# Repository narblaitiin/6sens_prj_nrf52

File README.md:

# 6Sens: inSitu Seismic System for Slope Stability Sensing

## Desciption
The goal is to develop a warning system on the analysis of the evolution of the micro-seismic activity generated before the instability is triggered. The method uses a multitude of low-cost seismic sensors deployed in-situ in a network over the possibly unstable zone. The goal is to characterize the temporal evolution of seismic signals detected simultaneously by several sensors (i .e., co-detection). This method uses to its advantage the heterogeneity of the materials and the attenuation of the waves during their propagation in the material.

The design of these sensors is subject to certain technical constraints essential to good
operation of the project:

    - Be autonomous in energy, over a period of several months (so as not to have to return to site, often dangerous).
    - Be robust, reliable and adapted to extreme climatic conditions (cold, hot, humidity).
    - All sensors in the network must be synchronized precisely enough to perform the analysis (about 1/10 second).
    - Be able to communicate information in real time – or near – measurements to a gateway that will retransmit the data to a dedicated website.
    - Be produced at low cost (to install a large-scale network, and have the possibility of to install sensors in hazardous areas with the possibility of losing them).

## Hardware description
### Geophone sensor
The choice fell on omni geometric sensors from Geospace Technologies such Omni-X-LT or GS-ONE. Seismic geophone is a type of sensor that converts ground movement or a kind vibration into voltage, which could be acquired by an acquisition system. The deviation of this mesured voltage from the base line is called the geophone response and is analysed and for monitoring vibration generated by nature in our case.

The frequency response of the geophone is a kind of harmonic oscillator, which is deternined by corner frequency, around 15Hz for the chosen sensors and damping (typically 0.7 for our case).
Our application require the full wave to be sued and the three-component 3C geophones is used (Omni-X-LT or GS-ONE).
For more information, please to refer to : https://www.geospace.com/products/sensors/

### Amplification/Filtering board
The specifications inform us about the bandwidth of the filtering to be carried out: from 20Hz at 100Hz. So we have to build a band-pass filter having an amplification almost constant on this band and rejects frequencies outside this band. Moreover, the signal will have to be amplified in order to obtain a complete dynamic range between 0 and 3.3V without saturation. Below are listed the
parameters of the different filters that will make up the amplification and filtering card :

    - Filter 1 : active bandpass filter, gain : 33dB, low frequency : 7Hz, high frequency : 154Hz
    - Filter 2 : passive low-pass filter, no gain, cut frequency : 106Hz
    - Filter 3 : active low-pass filter, gain : 6dB, cut frequency : 234Hz

### CPU/Radio board for test
The choice fell on Cicerone MKR main board. Move-X Cicerone LoRa/GNSS Board is a high-performance, low-power, Arduino MKR-compatible development board based on the MAMWLE LoRa Module and the u-blox MAX-M10S GNSS Module. The Cicerone Board delivers best-in-class GNSS, long-range wireless connection, and high-performance MCU processing in a low-power solution for optimal battery life. The Cicerone Board allows users to build tracking applications worldwide with meter-level accuracy and to communicate long-range, low-power data via LoRaWAN. The integrated Li-Po charging circuit enables the Cicerone Board to manage battery charging through the USB port.

### CPU/Radio board for POC
The choice was made to manufacture our own PCB. It has three parts: the MAMWLE-01 radio chipset to transmit LoRaWAN packets (based on an STM32WLE5jx), a UWB chipset DW1000 to measure distance between two sensors and an analog part to supply radio chipset (solar panel or/and Li-Po battery). Connectors (Arduino MKR-compatible) have also been added to insert the seismic sensor amplification/filtering board.

## Firmware description
For this project, the use of Zephyr RTOS has been retained. To see what is Zephyr RTOS and how to install it on your computer, go to https://docs.zephyrproject.org/latest/develop/getting_started/index.html (it supports Linux OS, Windows OS and macOS).

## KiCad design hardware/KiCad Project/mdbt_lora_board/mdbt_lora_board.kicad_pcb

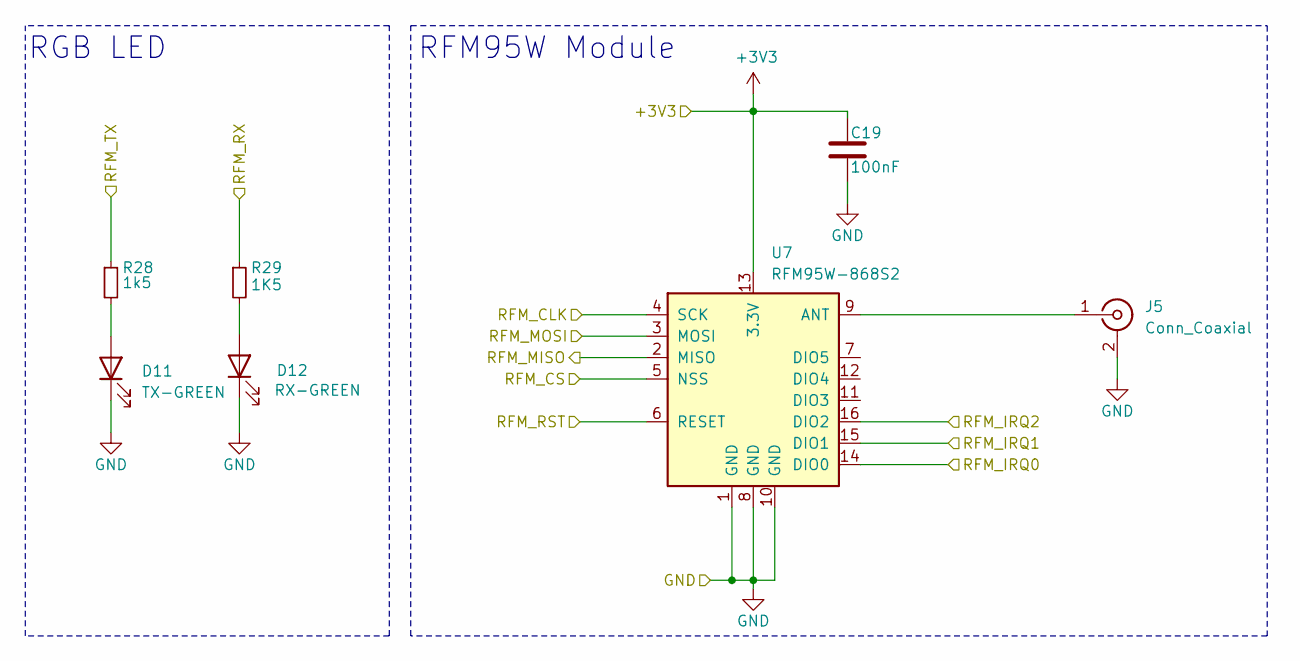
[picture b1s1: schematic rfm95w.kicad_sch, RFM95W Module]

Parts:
C19: 100nF; C_0603_1608Metric; MPN GCM188R71H104JA57D
D11: TX-GREEN; LED_0603_1608Metric; MPN LTST-C191KGKT
D12: RX-GREEN; LED_0603_1608Metric; MPN LTST-C191KGKT
J5: Conn_Coaxial; U.FL_Hirose_U.FL-R-SMT-1_Vertical; MPN U.FL-R-SMT-1(01)
R28: 1k5; R_0603_1608Metric; MPN RC0603FR-071K5L
R29: 1K5; R_0603_1608Metric; MPN RC0603JR-071K5L
U7: RFM95W-868S2; HOPERF_RFM9XW_SMD; MPN RFM95W-868S2

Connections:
+3V3: C19.1, U7.13 (3.3V); also elsewhere on the board
/MDBT50Q-1MV2 (nRF52840)/RFM_CLK: U7.4 (SCK); also elsewhere on the board
/MDBT50Q-1MV2 (nRF52840)/RFM_CS: U7.5 (NSS); also elsewhere on the board
/MDBT50Q-1MV2 (nRF52840)/RFM_IRQ0: U7.14 (DIO0); also elsewhere on the board
/MDBT50Q-1MV2 (nRF52840)/RFM_IRQ1: U7.15 (DIO1); also elsewhere on the board
/MDBT50Q-1MV2 (nRF52840)/RFM_IRQ2: U7.16 (DIO2); also elsewhere on the board
/MDBT50Q-1MV2 (nRF52840)/RFM_MISO: U7.2 (MISO); also elsewhere on the board
/MDBT50Q-1MV2 (nRF52840)/RFM_MOSI: U7.3 (MOSI); also elsewhere on the board
/MDBT50Q-1MV2 (nRF52840)/RFM_RST: U7.6 (RESET); also elsewhere on the board
/MDBT50Q-1MV2 (nRF52840)/RFM_RX: R29.1; also elsewhere on the board
/MDBT50Q-1MV2 (nRF52840)/RFM_TX: R28.1; also elsewhere on the board
GND: C19.2, D11.1 (K), D12.1 (K), J5.2 (Ext), U7.1 (GND), U7.8 (GND), U7.10 (GND); also elsewhere on the board
unnamed: D11.2 (A), R28.2
unnamed: D12.2 (A), R29.2
unnamed: J5.1 (In), U7.9 (ANT)

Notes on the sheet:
RFM95W Module
RGB LED

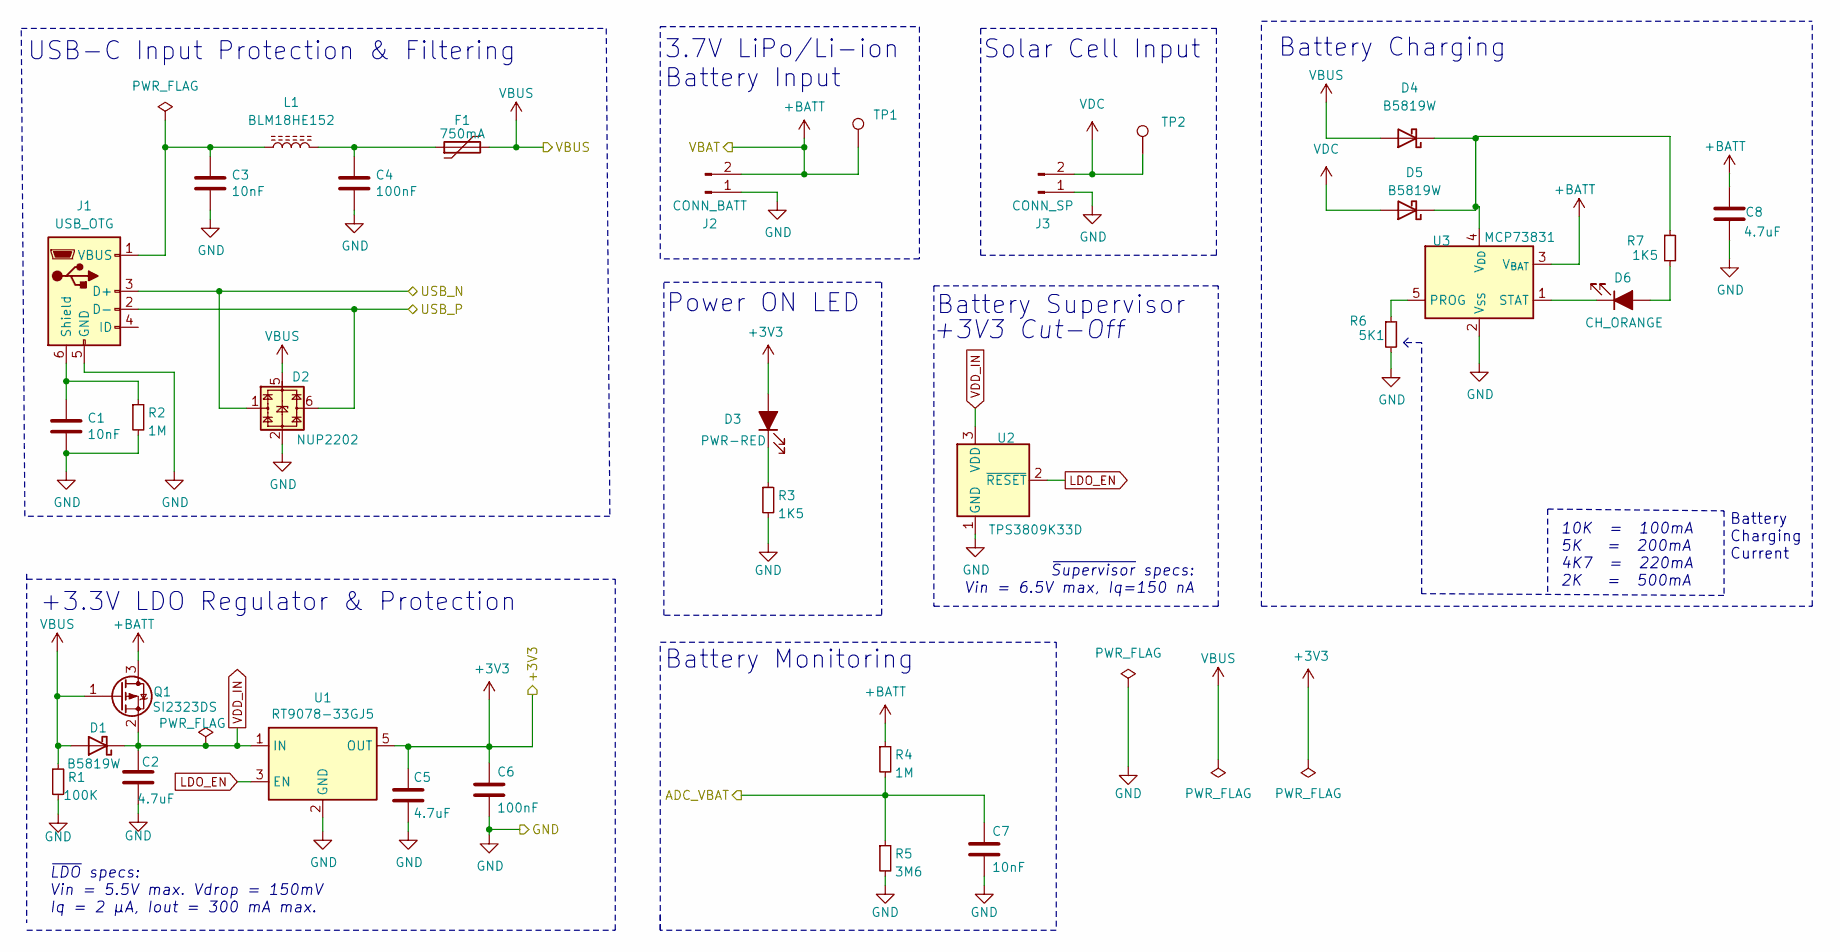
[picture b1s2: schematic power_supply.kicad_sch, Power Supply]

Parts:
C1, C7: 10nF; C_0603_1608Metric; MPN GRM1885C1H103JA01D
C2, C5, C8: 4.7uF; C_0603_1608Metric; MPN GRM188C81E475KE11D
C3: 10nF; C_0603_1608Metric; MPN GRM1885C1H103JA01D; LCSC_Part# Murata Electronics
C4, C6: 100nF; C_0603_1608Metric; MPN GCM188R71H104JA57D
D1, D4, D5: B5819W; D_SOD-123; MPN B5819W
D2: NUP2202; SOT-363_SC-70-6; MPN NUP2202W1T2G
D3: PWR-RED; LED_0603_1608Metric; MPN LTST-C191KRKT
D6: CH_ORANGE; LED_0603_1608Metric; MPN LTST-C191KFKT
F1: 750mA; Fuse_0805_2012Metric; MPN SMD0805B075TF
J1: USB_OTG; USB_Micro-B_Amphenol_10103594-0001LF_Horizontal; MPN 10103594-0001LF
J2: CONN_BATT; PinSocket_1x02_P2.00mm_Vertical; MPN DNM
J3: CONN_SP; PinSocket_1x02_P2.00mm_Vertical; MPN DNM
L1: BLM18HE152; L_0603_1608Metric; MPN BLM18HE152SN1D
Q1: SI2323DS; SOT-23-3; MPN SI2323DS-T1-GE3
R1: 100K; R_0603_1608Metric; MPN RC0603FR-07100KL
R2, R4: 1M; R_0603_1608Metric; MPN RC0603FR-071ML
R3, R7: 1K5; R_0603_1608Metric; MPN RC0603FR-071K5L
R5: 3M6; R_0603_1608Metric; MPN RC0603FR-073M6L
R6: 5K1; R_0603_1608Metric; MPN RC0603FR-075K1L
TP1, TP2: TestPoint; TestPoint_THTPad_D1.5mm_Drill0.7mm
U1: RT9078-33GJ5; TSOT-23-5; MPN RT9078-33GJ5
U2: TPS3809K33D; SOT-23-3; MPN TPS3809K33DBVRG4
U3: MCP73831; SOT-23-5; MPN MCP73831T-2ACI/OT

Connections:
+3V3: C5.1, C6.1, D3.2 (A), U1.5 (OUT); also elsewhere on the board
+BATT: C8.1, J2.2, Q1.3 (D), R4.1, TP1.1, U3.3 (V_{BAT}); also elsewhere on the board
/MDBT50Q-1MV2 (nRF52840)/ADC_VBAT: C7.1, R4.2, R5.1; also elsewhere on the board
/MDBT50Q-1MV2 (nRF52840)/USB_N: D2.1, J1.3 (D+); also elsewhere on the board
/MDBT50Q-1MV2 (nRF52840)/USB_P: D2.6, J1.2 (D-); also elsewhere on the board
GND: C1.1, C2.2, C3.2, C4.2, C5.2, C6.2, C7.2, C8.2, D2.2, J1.5 (GND), J2.1, J3.1, R1.2, R2.2, R3.2, R5.2, R6.2, U1.2 (GND), U2.1 (GND), U3.2 (V_{SS}); also elsewhere on the board
LDO_EN: U1.3 (EN), U2.2 (~RESET)
unnamed: C4.1, F1.1, L1.2
unnamed: D3.1 (K), R3.1
unnamed: D4.1 (K), D5.1 (K), R7.1, U3.4 (V_{DD})
unnamed: D6.2 (A), R7.2
unnamed: D6.1 (K), U3.1 (STAT)
unnamed: C1.2, J1.6 (Shield), R2.1
unnamed: C3.1, J1.1 (VBUS), L1.1
unnamed: R6.1, U3.5 (PROG)
VBUS: D1.2 (A), D2.5, D4.2 (A), F1.2, Q1.1 (G), R1.1; also elsewhere on the board
VDC: D5.2 (A), J3.2, TP2.1
VDD_IN: C2.1, D1.1 (K), Q1.2 (S), U1.1 (IN), U2.3 (VDD)

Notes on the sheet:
Battery Charging
3.7V LiPo/Li-ion Battery Input
Solar Cell Input
Power ON LED
Battery Monitoring
+3.3V LDO Regulator & Protection
10K = 100mA 5K = 200mA 4K7 = 220mA 2K = 500mA
USB-C Input Protection & Filtering
Battery Charging Current
~{Supervisor} specs: Vin = 6.5V max, Iq=150 nA
Battery Supervisor
~{LDO} specs: Vin = 5.5V max. Vdrop = 150mV Iq = 2 μA, Iout = 300 mA max.
+3V3 Cut-Off

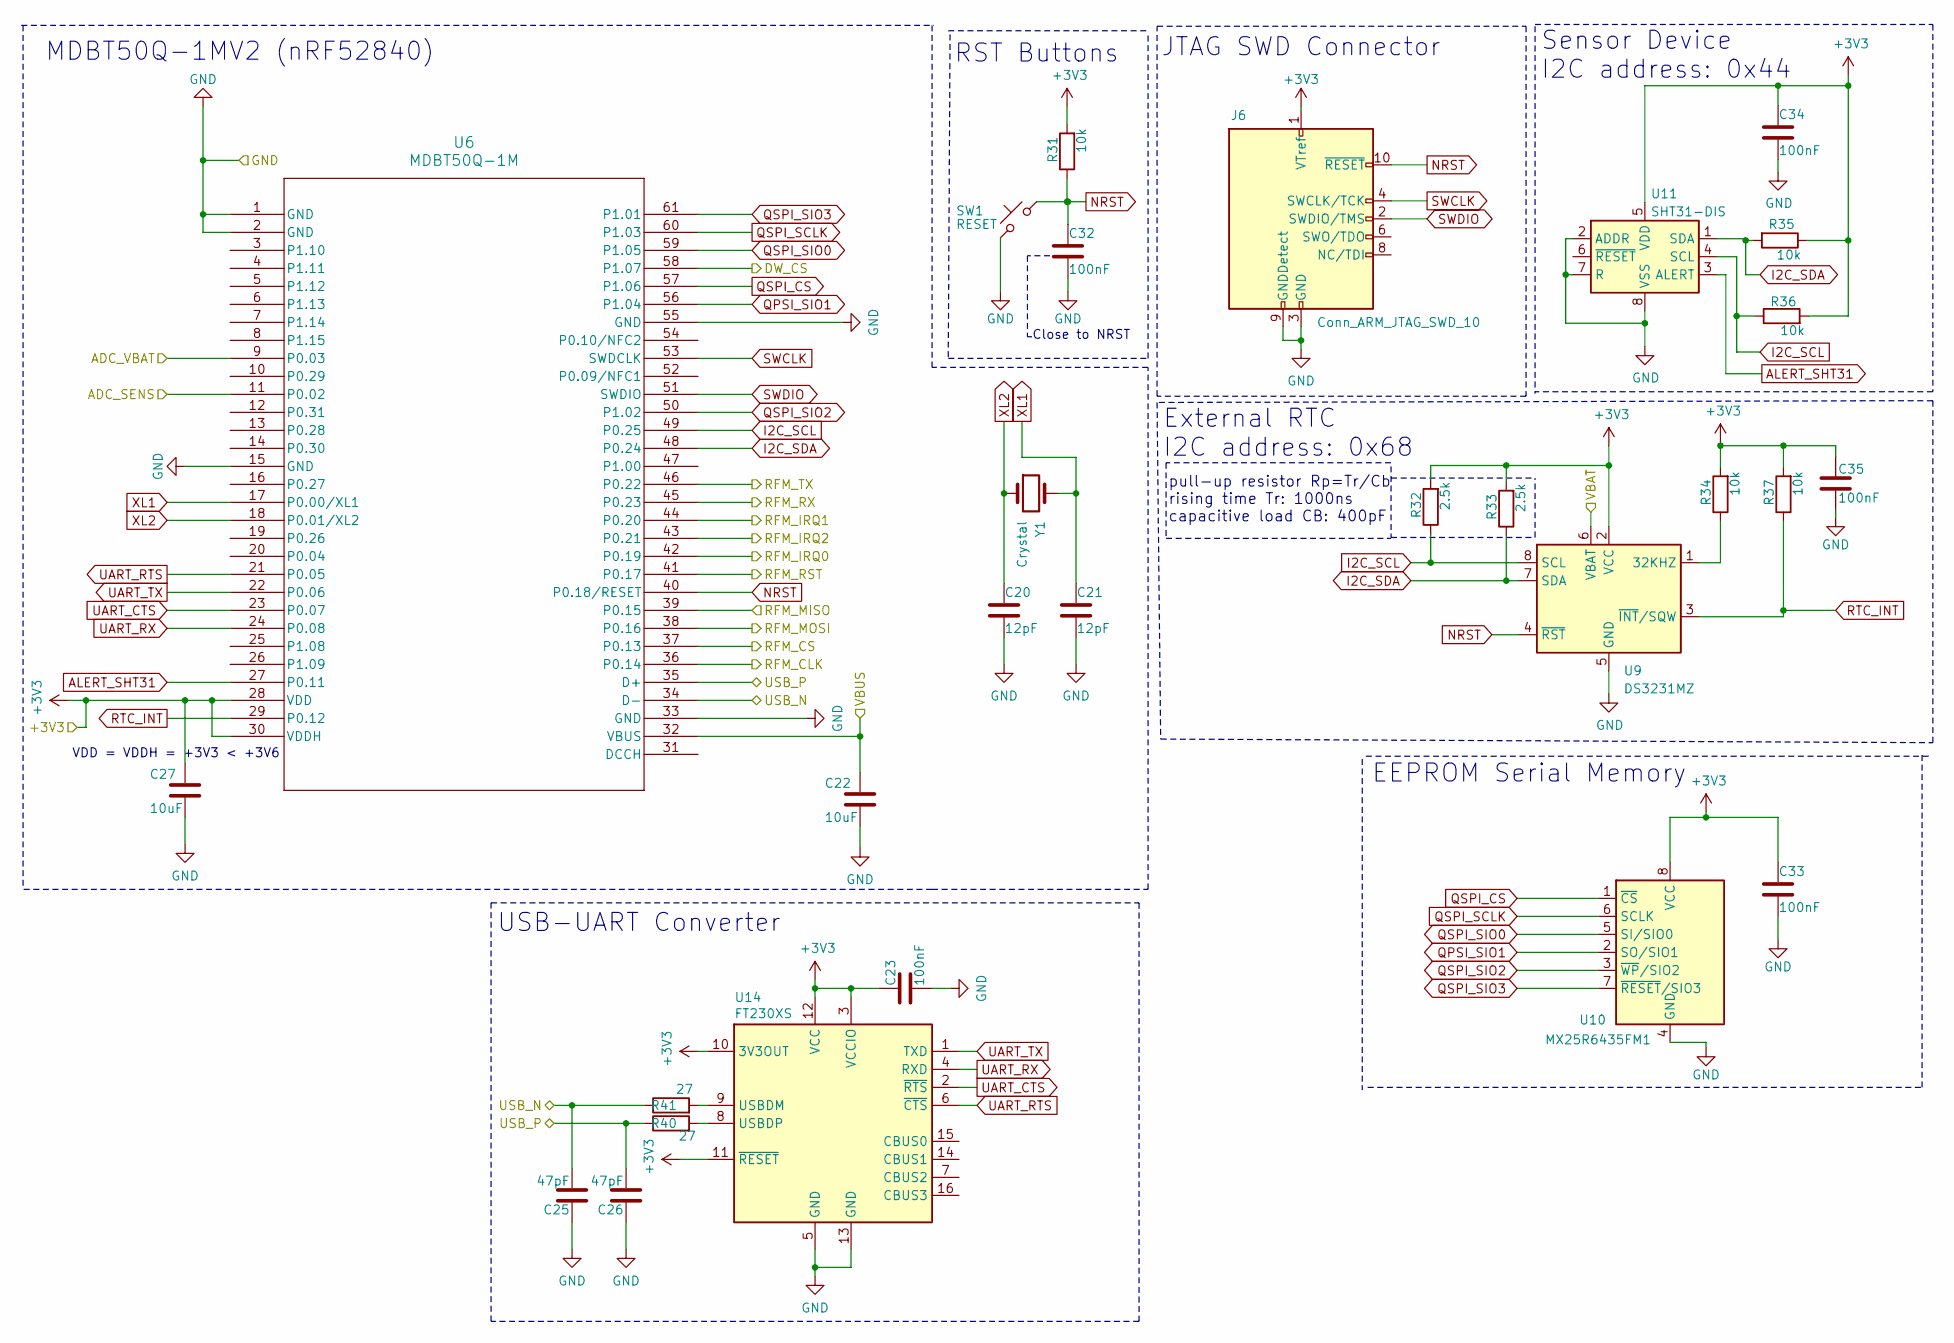
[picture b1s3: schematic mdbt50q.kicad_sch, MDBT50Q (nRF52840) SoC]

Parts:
C20, C21: 12pF; C_0603_1608Metric; MPN GRM1885C1H120JA01D
C22, C27: 10uF; C_0603_1608Metric; MPN GRM188R61E106KA73D
C23, C32, C33, C34, C35: 100nF; C_0603_1608Metric; MPN GCM188R71H104JA57D
C25, C26: 47pF; C_0603_1608Metric; MPN GRM1885C1H470JA01D
J6: Conn_ARM_JTAG_SWD_10; PinHeader_2x05_P1.27mm_Vertical_SMD; MPN 20021121-00010C4LF
R31, R34, R35, R36, R37: 10k; R_0603_1608Metric; MPN RC0603FR-0710KL
R32, R33: 2.5k; R_0603_1608Metric; MPN RC0603FR-072K5L
R40, R41: 27; R_0603_1608Metric; MPN RC0603FR-0727RL
SW1: RESET; SW_Push_1P1T_NO_Vertical_Wuerth_434133025816; MPN 434133025816
U6: MDBT50Q-1M; MDBT50Q-1M_RAY; MPN MDBT50Q-1MV2
U9: DS3231MZ; SOIC-8_3.9x4.9mm_P1.27mm; MPN DS3231MZ+TRL
U10: MX25R6435FM1; SOP-8_5.28x5.23mm_P1.27mm; MPN MX25R6435FM2IL0
U11: SHT31-DIS; Sensirion_DFN-8-1EP_2.5x2.5mm_P0.5mm_EP1.1x1.7mm; MPN SHT31-DIS-P2.5KS
U14: FT230XS; SSOP-16_3.9x4.9mm_P0.635mm; MPN FT230XS-R
Y1: Crystal; Crystal_SMD_3215-2Pin_3.2x1.5mm; MPN CM315D32768HZFT

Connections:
+3V3: C23.1, C27.1, C33.1, C34.1, C35.1, J6.1 (VTref), R31.2, R32.2, R33.2, R34.2, R35.1, R36.2, R37.2, U6.28 (VDD), U6.30 (VDDH), U9.2 (VCC), U10.8 (VCC), U11.5 (VDD), U14.3 (VCCIO), U14.10 (3V3OUT), U14.11 (~RESET), U14.12 (VCC); also elsewhere on the board
+BATT: U9.6 (VBAT); also elsewhere on the board
/Ampliflying and Filtering/ADC_SENS: U6.11 (P0.02); also elsewhere on the board
/MDBT50Q-1MV2 (nRF52840)/ADC_VBAT: U6.9 (P0.03); also elsewhere on the board
/MDBT50Q-1MV2 (nRF52840)/DW_CS: U6.58 (P1.07)
/MDBT50Q-1MV2 (nRF52840)/RFM_CLK: U6.36 (P0.14); also elsewhere on the board
/MDBT50Q-1MV2 (nRF52840)/RFM_CS: U6.37 (P0.13); also elsewhere on the board
/MDBT50Q-1MV2 (nRF52840)/RFM_IRQ0: U6.42 (P0.19); also elsewhere on the board
/MDBT50Q-1MV2 (nRF52840)/RFM_IRQ1: U6.44 (P0.20); also elsewhere on the board
/MDBT50Q-1MV2 (nRF52840)/RFM_IRQ2: U6.43 (P0.21); also elsewhere on the board
/MDBT50Q-1MV2 (nRF52840)/RFM_MISO: U6.39 (P0.15); also elsewhere on the board
/MDBT50Q-1MV2 (nRF52840)/RFM_MOSI: U6.38 (P0.16); also elsewhere on the board
/MDBT50Q-1MV2 (nRF52840)/RFM_RST: U6.41 (P0.17); also elsewhere on the board
/MDBT50Q-1MV2 (nRF52840)/RFM_RX: U6.45 (P0.23); also elsewhere on the board
/MDBT50Q-1MV2 (nRF52840)/RFM_TX: U6.46 (P0.22); also elsewhere on the board
/MDBT50Q-1MV2 (nRF52840)/USB_N: C25.2, R41.1, U6.34 (D-); also elsewhere on the board
/MDBT50Q-1MV2 (nRF52840)/USB_P: C26.2, R40.1, U6.35 (D+); also elsewhere on the board
ALERT_SHT31: U6.27 (P0.11), U11.3 (ALERT)
GND: C20.2, C21.2, C22.2, C23.2, C25.1, C26.1, C27.2, C32.2, C33.2, C34.2, C35.2, J6.3 (GND), J6.5 (GND), J6.9 (GNDDetect), SW1.1, U6.1 (GND), U6.2 (GND), U6.15 (GND), U6.33 (GND), U6.55 (GND), U9.5 (GND), U10.4 (GND), U11.2 (ADDR), U11.7 (R), U11.8 (VSS), U11.9 (VSS), U14.5 (GND), U14.13 (GND); also elsewhere on the board
I2C_SCL: R32.1, R36.1, U6.49 (P0.25), U9.8 (SCL), U11.4 (SCL)
I2C_SDA: R33.1, R35.2, U6.48 (P0.24), U9.7 (SDA), U11.1 (SDA)
NRST: C32.1, J6.10 (~RESET), R31.1, SW1.2, U6.40 (P0.18/RESET), U9.4 (~RST)
unnamed: R34.1, U9.1 (32KHZ)
unnamed: R41.2, U14.9 (USBDM)
unnamed: R40.2, U14.8 (USBDP)
QPSI_SIO1: U6.56 (P1.04), U10.2 (SO/SIO1)
QSPI_CS: U6.57 (P1.06), U10.1 (~CS)
QSPI_SCLK: U6.60 (P1.03), U10.6 (SCLK)
QSPI_SIO0: U6.59 (P1.05), U10.5 (SI/SIO0)
QSPI_SIO2: U6.50 (P1.02), U10.3 (~WP/SIO2)
QSPI_SIO3: U6.61 (P1.01), U10.7 (~RESET/SIO3)
RTC_INT: R37.1, U6.29 (P0.12), U9.3 (~INT/SQW)
SWCLK: J6.4 (SWCLK/TCK), U6.53 (SWDCLK)
SWDIO: J6.2 (SWDIO/TMS), U6.51 (SWDIO)
UART_CTS: U6.23 (P0.07), U14.2 (~RTS)
UART_RTS: U6.21 (P0.05), U14.6 (~CTS)
UART_RX: U6.24 (P0.08), U14.4 (RXD)
UART_TX: U6.22 (P0.06), U14.1 (TXD)
VBUS: C22.1, U6.32 (VBUS); also elsewhere on the board
XL1: C21.1, U6.17 (P0.00/XL1), Y1.2
XL2: C20.1, U6.18 (P0.01/XL2), Y1.1

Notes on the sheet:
MDBT50Q-1MV2 (nRF52840)
JTAG SWD Connector
External RTC I2C address: 0x68
Close to NRST
pull-up resistor Rp=Tr/Cb rising time Tr: 1000ns capacitive load CB: 400pF
Sensor Device I2C address: 0x44
USB-UART Converter
EEPROM Serial Memory
VDD = VDDH = +3V3 < +3V6
RST Buttons

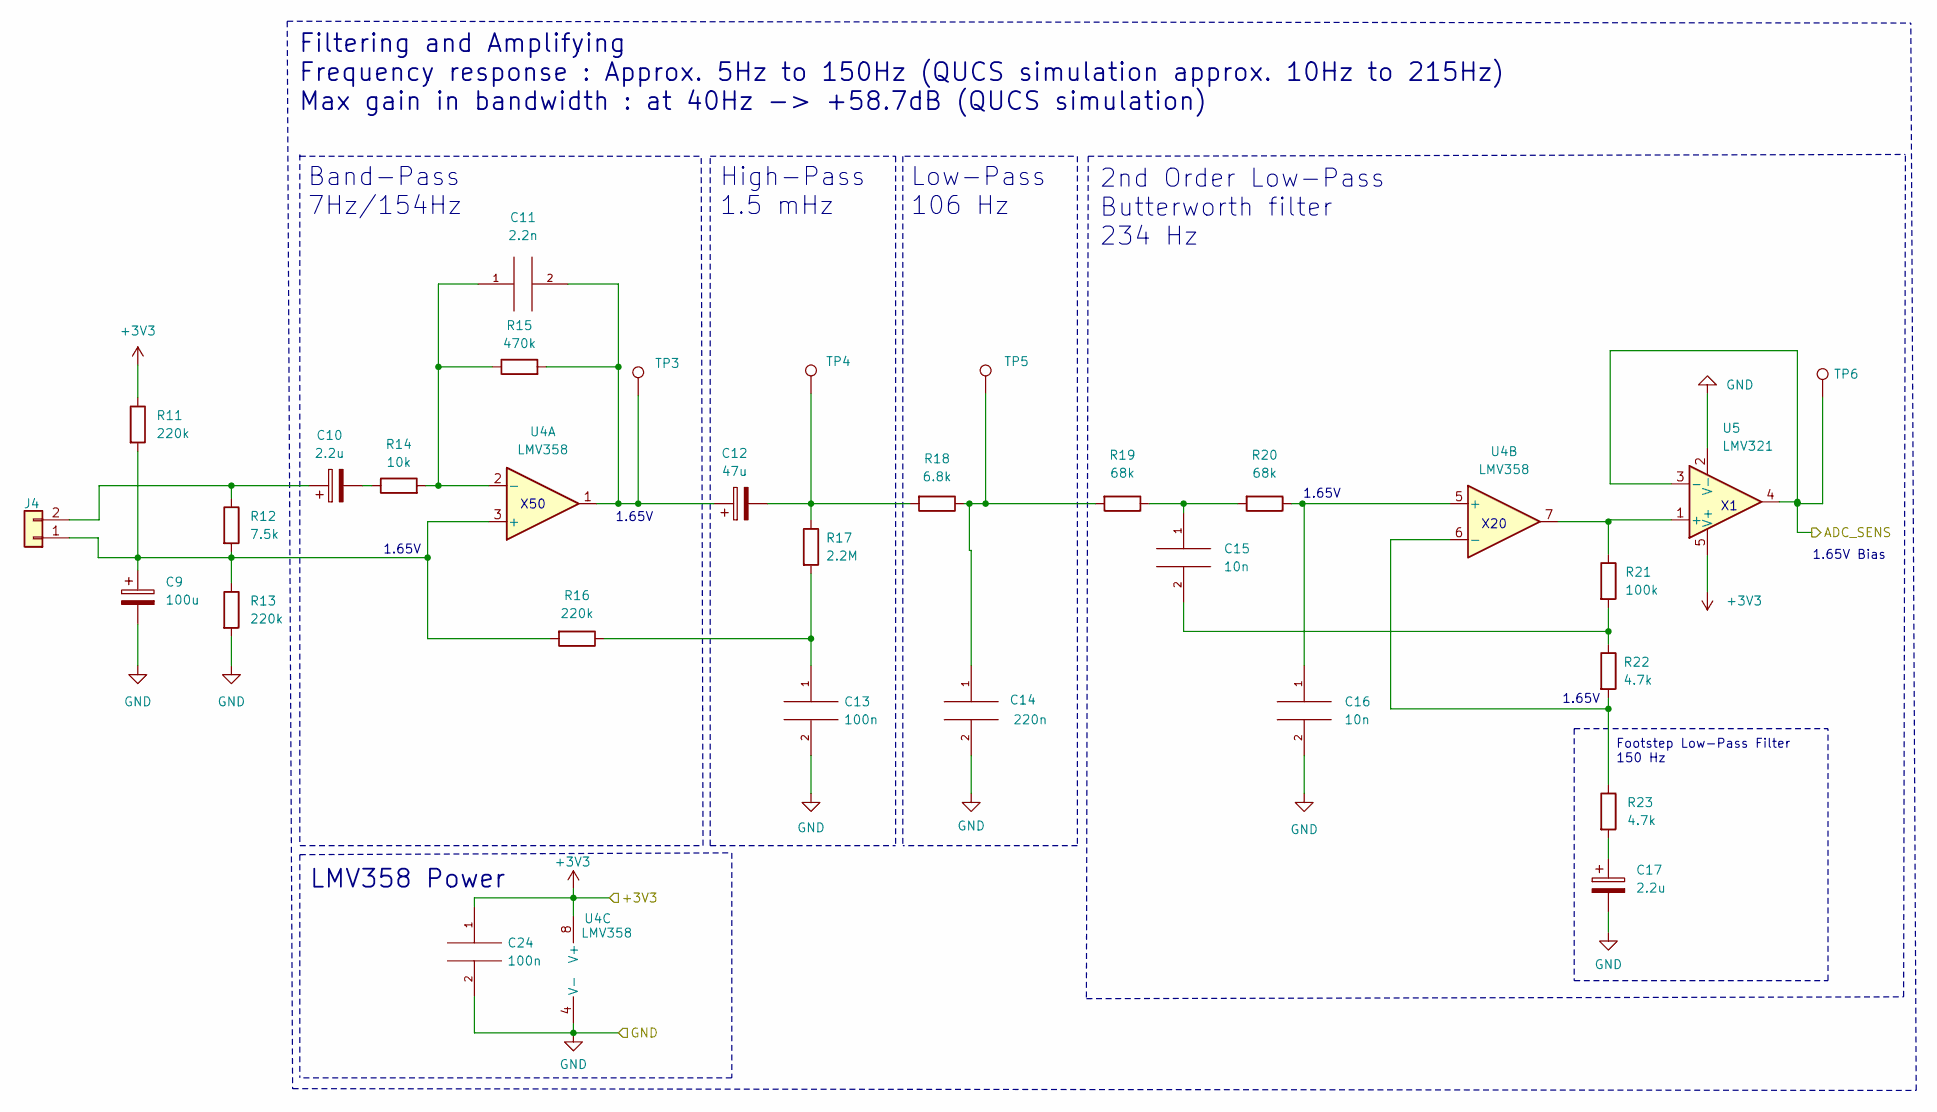
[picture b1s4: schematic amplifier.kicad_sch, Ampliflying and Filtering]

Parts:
C9: 100u; C_1206_3216Metric; MPN GRM31CR60J107KEA8L
C10, C17: 2.2u; C_0603_1608Metric; MPN GRM188R61E225KA12D
C11: 2.2n; C_0603_1608Metric; MPN GRM1885C1H222FA01D
C12: 47u; C_1206_3216Metric; MPN GRM31CR61A476KE15L
C13, C24: 100n; C_0603_1608Metric; MPN GCM188R71H104JA57D
C14: 220n; C_0603_1608Metric; MPN GRM188R71A224JA01D
C15, C16: 10n; C_0603_1608Metric; MPN GRM1885C1H103JA01D
J4: Conn_01x02; JST_PH_S2B-PH-SM4-TB_1x02-1MP_P2.00mm_Horizontal; MPN S2B-PH-SM4-TB
R11, R13, R16: 220k; R_0603_1608Metric; MPN RC0603FR-07220KL
R12: 7.5k; R_0603_1608Metric; MPN RC0603FR-077K5L
R14: 10k; R_0603_1608Metric; MPN RC0603FR-0710KL
R15: 470k; R_0603_1608Metric; MPN RC0603FR-07470KL
R17: 2.2M; R_0603_1608Metric; MPN RC0603FR-072M2L
R18: 6.8k; R_0603_1608Metric; MPN RC0603FR-076K8L
R19, R20: 68k; R_0603_1608Metric; MPN RC0603FR-076K8L
R21: 100k; R_0603_1608Metric; MPN RC0603FR-07100KL
R22, R23: 4.7k; R_0603_1608Metric; MPN RC0603FR-074K7L
TP3, TP4, TP5, TP6: TestPoint; TestPoint_THTPad_D1.5mm_Drill0.7mm
U4: LMV358; SOIC-8_3.9x4.9mm_P1.27mm; MPN LMV358IDRG4
U5: LMV321; SOT-23-5; MPN LMV321IDBVR

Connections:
+3V3: C24.1, R11.1, U4.8 (V+), U5.5 (V+); also elsewhere on the board
/Ampliflying and Filtering/ADC_SENS: TP6.1, U5.3 (-), U5.4; also elsewhere on the board
GND: C9.2, C13.2, C14.2, C16.2, C17.2, C24.2, R13.2, U4.4 (V-), U5.2 (V-); also elsewhere on the board
unnamed: C10.2, R14.1
unnamed: C11.2, C12.1, R15.2, TP3.1, U4.1
unnamed: C12.2, R17.1, R18.2, TP4.1
unnamed: C13.1, R16.1, R17.2
unnamed: C14.1, R18.1, R19.2, TP5.1
unnamed: C15.1, R19.1, R20.2
unnamed: C15.2, R21.2, R22.1
unnamed: C17.1, R23.2
unnamed: C9.1, J4.1, R11.2, R12.2, R13.1, R16.2, U4.3 (+)
unnamed: C10.1, J4.2, R12.1
unnamed: C11.1, R14.2, R15.1, U4.2 (-)
unnamed: C16.1, R20.1, U4.5 (+)
unnamed: R22.2, R23.1, U4.6 (-)
unnamed: R21.1, U4.7, U5.1 (+)

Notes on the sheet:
High-Pass 1.5 mHz
1.65V
LMV358 Power
X20
2nd Order Low-Pass Butterworth filter 234 Hz
1.65V Bias
Low-Pass 106 Hz
Filtering and Amplifying Frequency response : Approx. 5Hz to 150Hz (QUCS simulation approx. 10Hz to 215Hz) Max gain in bandwidth : at 40Hz -> +58.7dB (QUCS simulation)
Footstep Low-Pass Filter 150 Hz
X50
Band-Pass 7Hz/154Hz

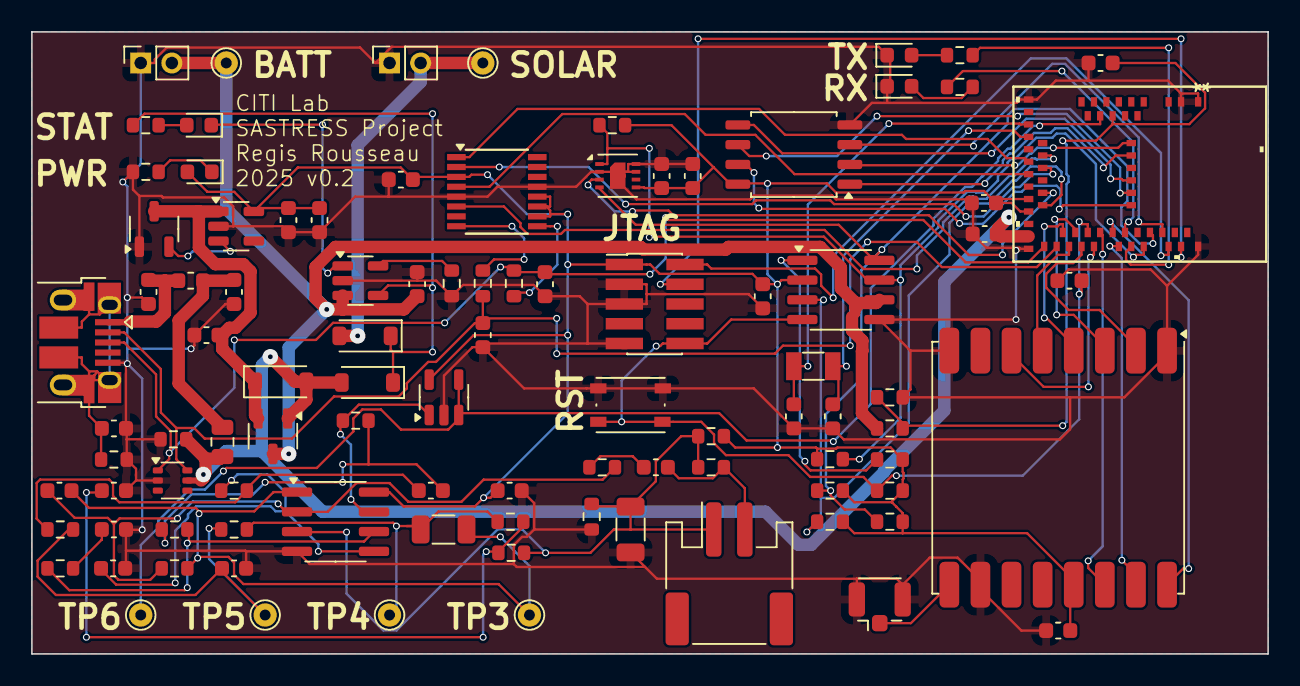
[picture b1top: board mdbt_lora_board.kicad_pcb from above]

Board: 2 copper layers, 79.5 x 40.0 mm, 97 parts (0 on the bottom side), 68 nets.

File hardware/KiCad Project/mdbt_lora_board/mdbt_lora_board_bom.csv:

Reference,Value,Qty,#,MPN,Manufacturer
"C1,C3,C7",10nF,3,1,GRM1885C1H103JA01D,-- mixed values --
"C2,C5,C8",4.7uF,3,2,GRM188C81E475KE11D,Murata Electronics
"C4,C6,C19,C23,C32,C33,C34,C35",100nF,8,3,GCM188R71H104JA57D,Murata Electronics
C9,100u,1,4,GRM31CR60J107KEA8L,Murata Electronics
"C10,C17",2.2u,2,5,GRM188R61E225KA12D,Murata Electronics
C11,2.2n,1,6,GRM1885C1H222FA01D,Murata Electronics
C12,47u,1,7,GRM31CR61A476KE15L,Murata Electronics
"C13,C24",100n,2,8,GCM188R71H104JA57D,Murata Electronics
C14,220n,1,9,GRM188R71A224JA01D,Murata Electronics
"C15,C16",10n,2,10,GRM1885C1H103JA01D,Murata Electronics
"C20,C21",12pF,2,11,GRM1885C1H120JA01D,Murata Electronics
"C22,C27",10uF,2,12,GRM188R61E106KA73D,Murata Electronics
"C25,C26",47pF,2,13,GRM1885C1H470JA01D,Murata Electronics
"D1,D4,D5",B5819W,3,14,B5819W,Good-Ark
D2,NUP2202,1,15,NUP2202W1T2G,Onsemi
D3,PWR-RED,1,16,LTST-C191KRKT,Lite-On Inc
D6,CH_ORANGE,1,17,LTST-C191KFKT,Lite-On Inc
D11,TX-GREEN,1,18,LTST-C191KGKT,Lite-On Inc
D12,RX-GREEN,1,19,LTST-C191KGKT,Lite-On Inc
F1,750mA,1,20,SMD0805B075TF,Yageo
J1,USB_OTG,1,21,10103594-0001LF,Amphenol ICC (FCI)
J2,CONN_BATT,1,22,DNM,
J3,CONN_SP,1,23,DNM,
J4,Conn_01x02,1,24,S2B-PH-SM4-TB,JST Sales America Inc
J5,Conn_Coaxial,1,25,U.FL-R-SMT-1(01),Hirose Electric Co Ltd
J6,Conn_ARM_JTAG_SWD_10,1,26,20021121-00010C4LF,Amphenol ICC (FCI)
L1,BLM18HE152,1,27,BLM18HE152SN1D,Murata Electronics
Q1,SI2323DS,1,28,SI2323DS-T1-GE3,Vishay Siliconix
R1,100K,1,29,RC0603FR-07100KL,Yageo
"R2,R4",1M,2,30,RC0603FR-071ML,Yageo
"R3,R7,R29",1K5,3,31,RC0603FR-072K49L,Yageo
R5,3M6,1,32,RC0603FR-073M6L,Yageo
R6,5K1,1,33,RC0603FR-075K1L,Yageo
"R11,R13,R16",220k,3,34,RC0603FR-07220KL,Yageo
R12,7.5k,1,35,RC0603FR-077K5L,Yageo
"R14,R31,R34,R35,R36,R37",10k,6,36,RC0603FR-0710KL,Yageo
R15,470k,1,37,RC0603FR-07470KL,Yageo
R17,2.2M,1,38,RC0603FR-072M2L,Yageo
R18,6.8k,1,39,RC0603FR-076K8L,Yageo
"R19,R20",68k,2,40,RC0603FR-076K8L,Yageo
R21,100k,1,41,RC0603FR-07100KL,Yageo
"R22,R23",4.7k,2,42,RC0603FR-074K7L,Yageo
R28,1k5,1,43,RC0603FR-071K5L,Yageo
"R32,R33",2.49k,2,44,RC0603FR-072K49L,Yageo
"R40,R41",27,2,45,RC0603FR-0727RL,Yageo
SW1,RESET,1,46,434133025816,Wurth Elektronik
"TP1,TP2,TP3,TP4,TP5,TP6",TestPoint,6,47,,
U1,RT9078-33GJ5,1,48,RT9078-33GJ5,Richtek USA Inc
U2,TPS3809K33D,1,49,TPS3809K33DBVRG4,Texas Instrument
U3,MCP73831,1,50,MCP73831T-2ACI/OT,Microchip Technology
U4,LMV358,1,51,LMV358IDRG4,Texas Instrument
U5,LMV321,1,52,LMV321IDBVR,Texas Instrument
U6,MDBT50Q-1M,1,53,MDBT50Q-1MV2,Raytac
U7,RFM95W-868S2,1,54,RFM95W-868S2,RF Solutions
U9,DS3231MZ,1,55, DS3231MZ+TRL,Analog Device
U10,MX25R6435FM1,1,56,MX25R6435FM2IL0,Macronix
U11,SHT31-DIS,1,57,SHT31-DIS-P2.5KS,Sensirion AG
U14,FT230XS,1,58,FT230XS-R,FTDI
Y1,Crystal,1,59,CM315D32768HZFT,Citizen Finedevice

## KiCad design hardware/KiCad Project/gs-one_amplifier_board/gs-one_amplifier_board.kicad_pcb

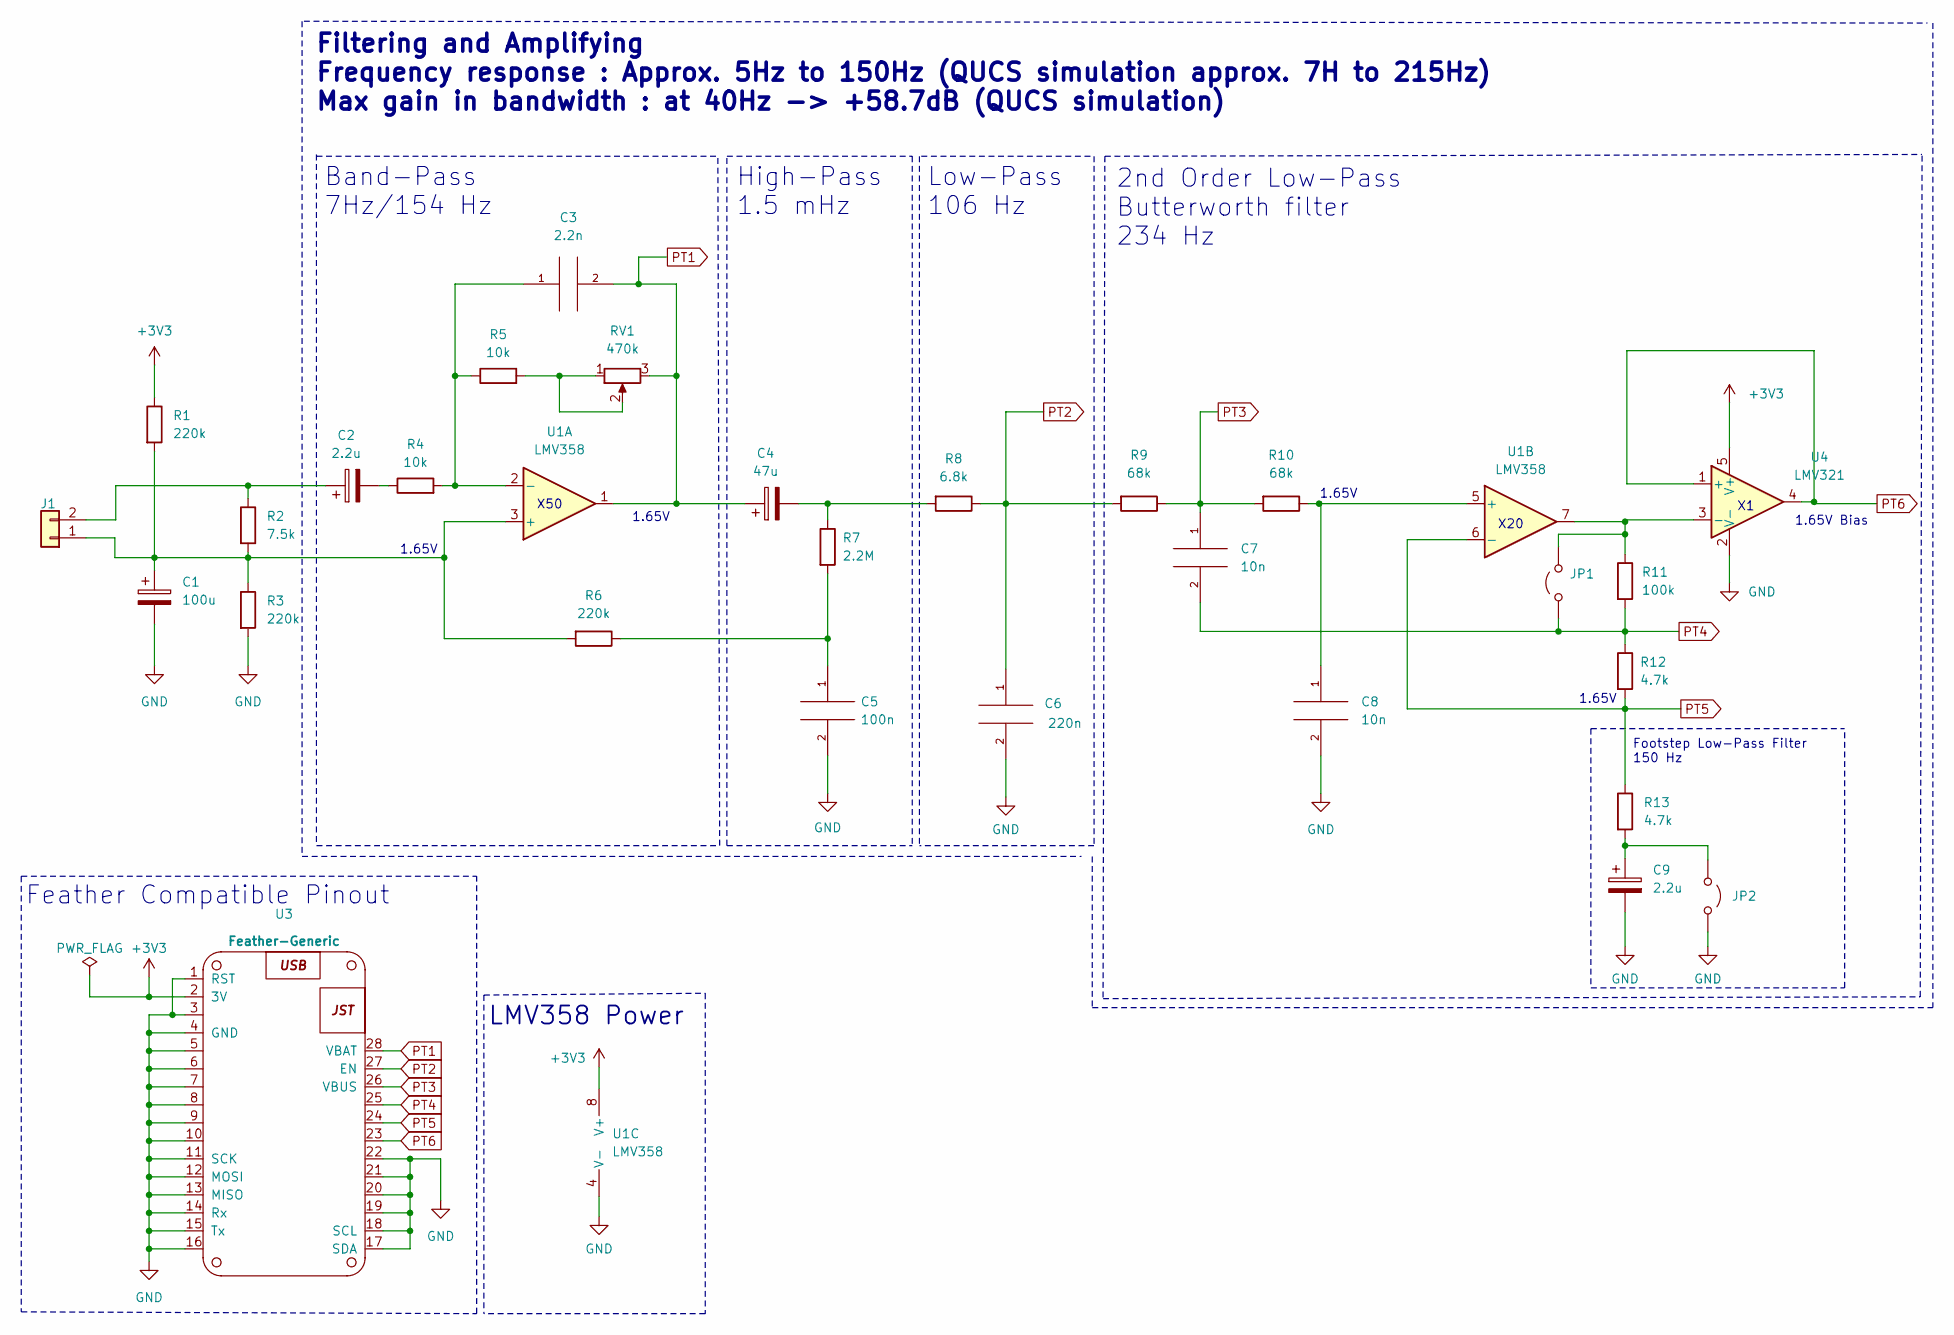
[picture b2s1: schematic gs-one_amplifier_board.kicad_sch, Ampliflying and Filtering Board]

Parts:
C1: 100u; C_1206_3216Metric; MPN GRM31CD80J107MEA8K
C2, C9: 2.2u; C_0603_1608Metric; MPN GRM188R61E106KA73J
C3: 2.2n; C_0603_1608Metric; MPN GRM1885C1H222FA01D
C4: 47u; C_0603_1608Metric; MPN GRM188R60J476ME01D
C5: 100n; C_0603_1608Metric; MPN GRM188R72A104KA35D
C6: 220n; C_0603_1608Metric; MPN GRM188R71E224KA88D
C7: 10n; C_0603_1608Metric; MPN GCM219R91H103KA37D
C8: 10n; C_0603_1608Metric; MPN GRM1885C1H103JA01D
J1: Conn_01x02; JST_PH_S2B-PH-SM4-TB_1x02-1MP_P2.00mm_Horizontal; MPN B2B-PH-SM4-TB(LF)(SN)
JP1, JP2: Jumper_2_Open; PinHeader_1x02_P1.27mm_Vertical
R1, R3, R6: 220k; R_0603_1608Metric; MPN RC0603FR-07220KL
R2: 7.5k; R_0603_1608Metric; MPN RC0603FR-077K5L
R4, R5: 10k; R_0603_1608Metric; MPN RC0603FR-0710KL
R7: 2.2M; R_0603_1608Metric; MPN RC0603FR-072M2L
R8: 6.8k; R_0603_1608Metric; MPN RC0603FR-076K8L
R9, R10: 68k; R_0603_1608Metric; MPN RC0603FR-076K8L
R11: 100k; R_0603_1608Metric; MPN RC0603FR-07100KL
R12, R13: 4.7k; R_0603_1608Metric; MPN RC0603FR-074K7L
RV1: 470k; Potentiometer_Bourns_3386P_Vertical; MPN 3386P-1-474LF
U1: LMV358; M08A-M; MPN LMV358IDR
U3: Feather-Generic; Feather-Generic-no-holes
U4: LMV321; DCK5

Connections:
+3V3: R1.1, U1.8 (V+), U3.2 (3V), U4.5 (V+)
GND: C1.2, C5.2, C6.2, C8.2, C9.2, JP2.1 (A), R3.2, U1.4 (V-), U3.1 (RST), U3.3, U3.4 (GND), U3.5, U3.6, U3.7, U3.8, U3.9, U3.10, U3.11 (SCK), U3.12 (MOSI), U3.13 (MISO), U3.14 (Rx), U3.15 (Tx), U3.16, U3.17 (SDA), U3.18 (SCL), U3.19, U3.20, U3.21, U3.22, U4.2 (V-)
unnamed: C2.2, R4.1
unnamed: C4.2, R7.1, R8.2
unnamed: C5.1, R6.1, R7.2
unnamed: C1.1, J1.1, R1.2, R2.2, R3.1, R6.2, U1.3 (+)
unnamed: C2.1, J1.2, R2.1
unnamed: JP1.2 (B), R11.1, U1.7, U4.3 (-)
unnamed: C9.1, JP2.2 (B), R13.2
unnamed: R5.2, RV1.1, RV1.2
unnamed: C3.1, R4.2, R5.1, U1.2 (-)
unnamed: C8.1, R10.1, U1.5 (+)
PT1: C3.2, C4.1, RV1.3, U1.1, U3.28 (VBAT)
PT2: C6.1, R8.1, R9.2, U3.27 (EN)
PT3: C7.1, R9.1, R10.2, U3.26 (VBUS)
PT4: C7.2, JP1.1 (A), R11.2, R12.1, U3.25
PT5: R12.2, R13.1, U1.6 (-), U3.24
PT6: U3.23, U4.1 (+), U4.4

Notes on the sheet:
1.65V
Filtering and Amplifying Frequency response : Approx. 5Hz to 150Hz (QUCS simulation approx. 7H to 215Hz) Max gain in bandwidth : at 40Hz -> +58.7dB (QUCS simulation)
1.65V Bias
Feather Compatible Pinout
Footstep Low-Pass Filter 150 Hz
High-Pass 1.5 mHz
Band-Pass 7Hz/154 Hz
Low-Pass 106 Hz
LMV358 Power
2nd Order Low-Pass Butterworth filter 234 Hz
X50
X20

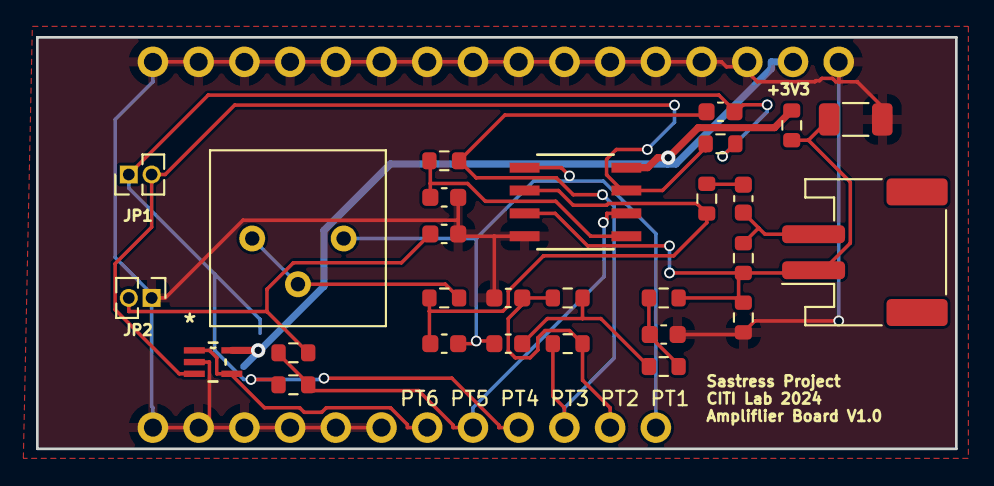
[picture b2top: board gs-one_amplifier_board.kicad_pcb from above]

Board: 2 copper layers, 51.1 x 22.9 mm, 29 parts (0 on the bottom side), 18 nets.

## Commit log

2025-03-25 add timestamp in payload
2025-03-25 test different brokers
2025-03-26 error in client_id code line
2025-03-27 on pending: password
2025-03-28 improve code with and without mqtt
2025-03-28 add laucher as service
2025-03-28 add method to put python script as launcher
2025-04-01 add time and date in payload
2025-04-01 add date and time in payload with custom format
2025-04-01 bug fixes in mqtt topic and port
2025-04-01 change how script lauch on startup
2025-04-01 add readme file to explain the process to put as servcie
2025-04-01 add Group=admin
2025-04-01 add ```` to gray out the code parts
2025-05-14 big upgrade
